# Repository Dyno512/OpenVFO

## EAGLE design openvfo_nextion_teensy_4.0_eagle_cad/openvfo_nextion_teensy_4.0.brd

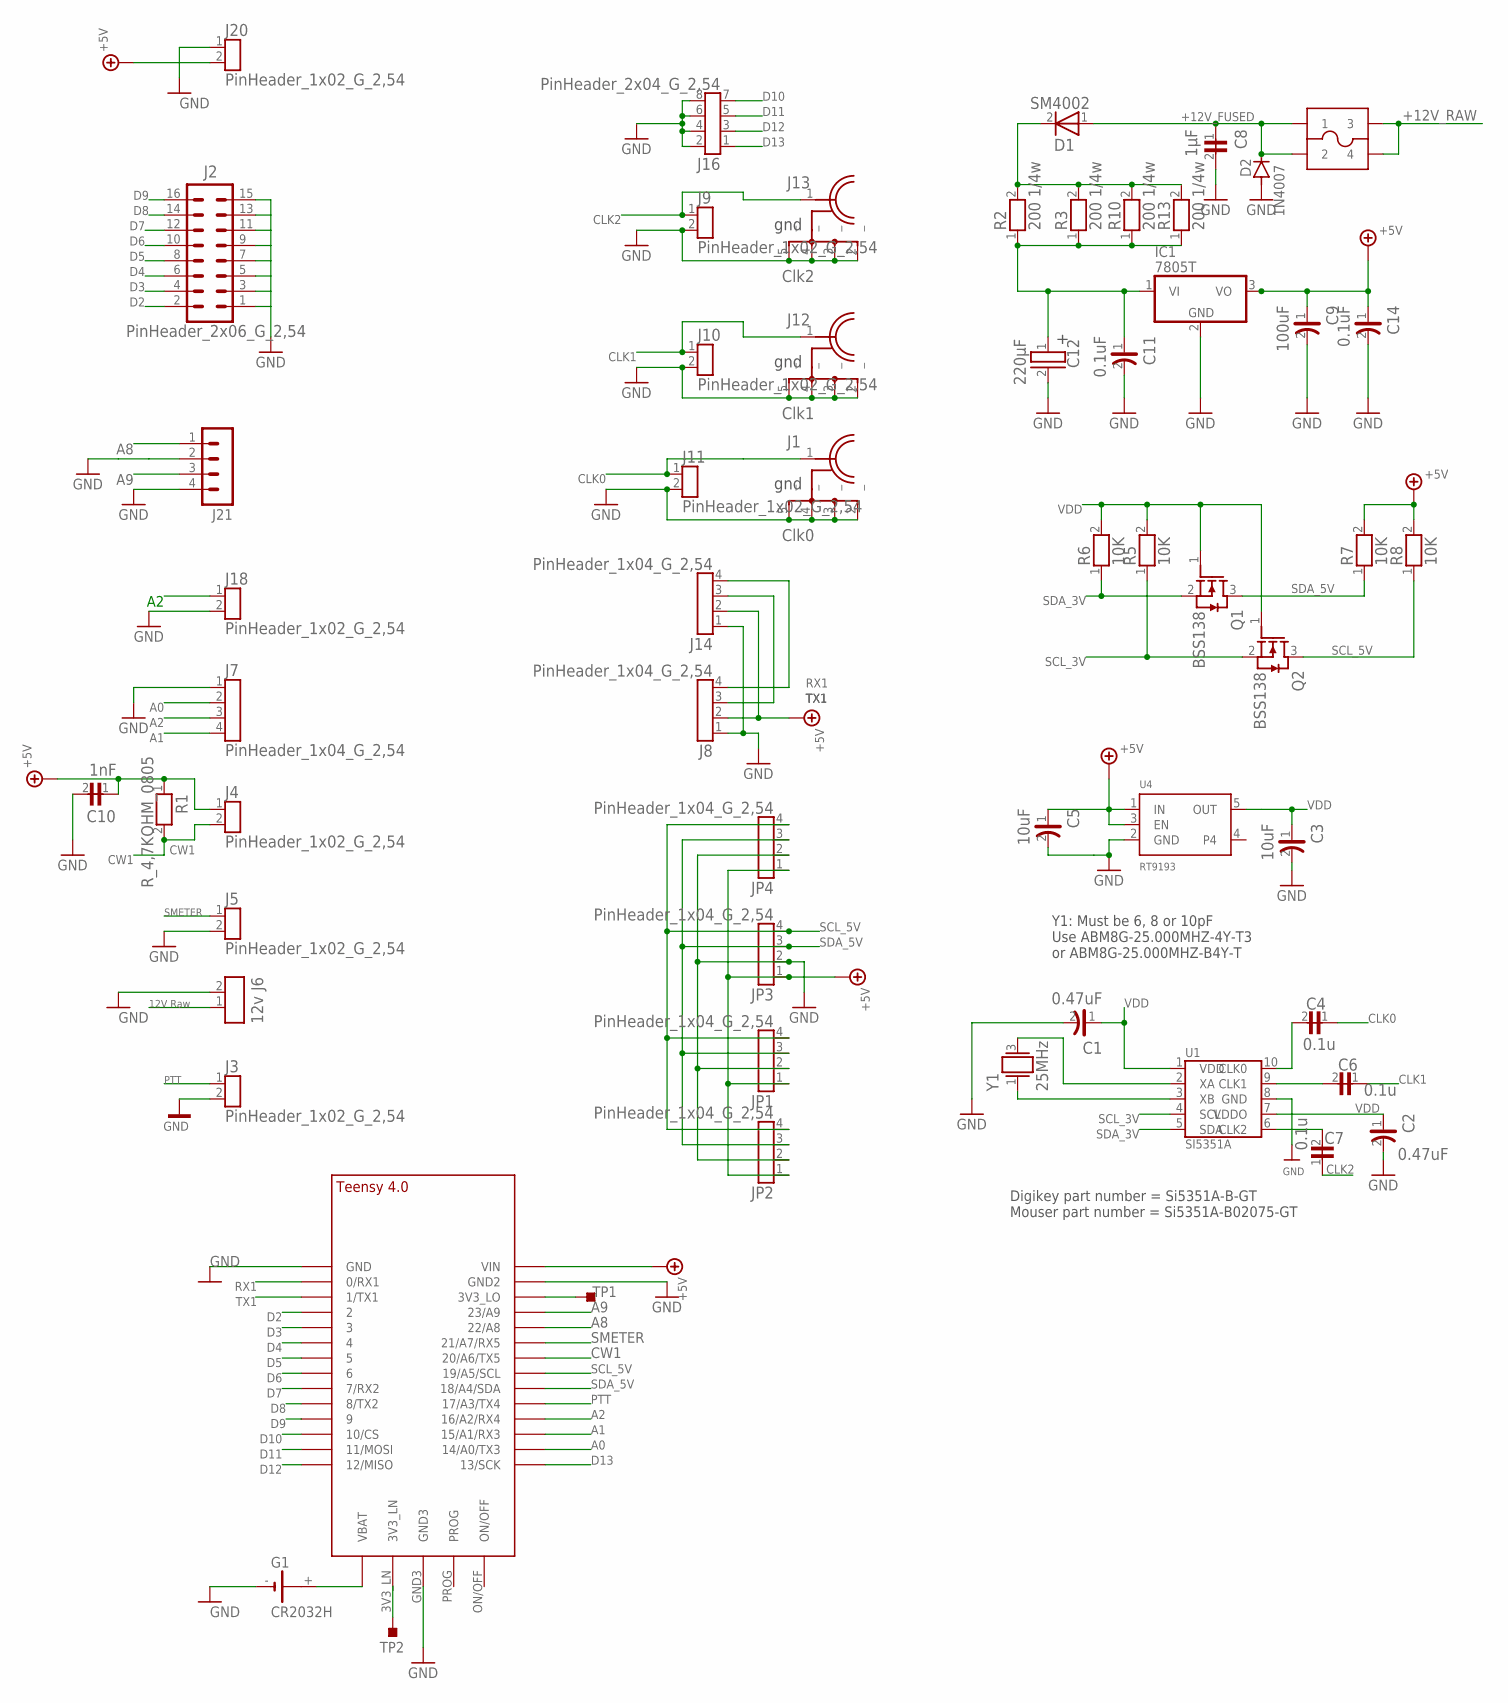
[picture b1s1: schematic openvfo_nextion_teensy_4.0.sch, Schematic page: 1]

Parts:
C1: 0.47uF; 0805_3
C2: 0.47uF; 0805_4
C3: 10uF; 0805_13
C4: 0.1u; 0805_81
C5: 10uF; 0805_12
C6: 0.1u; 0805_82
C7: 0.1u; 0805_83
C8: 1µF; 1206_84
C9: 100uF; 0805_95
C10: 1nF; 0805_23
C11: 0.1uF; 0805_89
C12: 220µF; D8R3,81_ELKO_104
C14: 0.1uF; 0805_96
D1: SM4002; MELF_85
D2: 1N4007; DO41-10
F1: SMALLFUSE
G1: CR2032H
IC1: 7805T; TO220H
J1: Clk0; SMA-EINBAUBUCHSE_67
J2: PinHeader_2x06_G_2,54; MA08-2
J3: PinHeader_1x02_G_2,54; STIFTLEISTE_1X02_G_2,54_17
J4: PinHeader_1x02_G_2,54; STIFTLEISTE_1X02_G_2,54_18
J5: PinHeader_1x02_G_2,54; STIFTLEISTE_1X02_G_2,54_19
J6: 12v; SL-MTA/2.54/2POL_20
J7: PinHeader_1x04_G_2,54; STIFTLEISTE_1X04_G_2,54_15
J8: PinHeader_1x04_G_2,54; STIFTLEISTE_1X04_G_2,54_22
J9: PinHeader_1x02_G_2,54; STIFTLEISTE_1X02_G_2,54_49
J10: PinHeader_1x02_G_2,54; STIFTLEISTE_1X02_G_2,54_50
J11: PinHeader_1x02_G_2,54; STIFTLEISTE_1X02_G_2,54_51
J12: Clk1; SMA-EINBAUBUCHSE_68
J13: Clk2; SMA-EINBAUBUCHSE_69
J14: PinHeader_1x04_G_2,54; STIFTLEISTE_1X04_G_2,54_70
J16: PinHeader_2x04_G_2,54; STIFTLEISTE_2X04_G_2,54_71
J18: PinHeader_1x02_G_2,54; STIFTLEISTE_1X02_G_2,54_97
J20: PinHeader_1x02_G_2,54; STIFTLEISTE_1X02_G_2,54_137
J21: MA04-1
JP1, JP2, JP3, JP4: PinHeader_1x04_G_2,54; STIFTLEISTE_1X04_G_2,54_14
Q1: BSS138; SOT23/3_7
Q2: BSS138; SOT23/3_8
R1: R_4,7KOHM_0805; 0805_21
R2: 200 1/4w; 0805_142
R3: 200 1/4w; 0805_145
R5: 10K; 0805_5
R6: 10K; 0805_6
R7: 10K; 0805_9
R8: 10K; 0805_10
R10: 200 1/4w; 0805_146
R13: 200 1/4w; 0805_147
TP1, TP2: TESTPOINT_TPS-PAD-036; TESTPOINT_PAD-036
U1: SI5351A; MSOP10/WB3X3/P0,5_0
U4: RT9193; SOT23-5_11
U$1: TEENSY_4.0
Y1: 25MHz; CFPX-104_1

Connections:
+5V: C5.1, C9.1, C10.1, C14.1, IC1.3 (VO), J4.1, J8.2, J14.2, J20.2, JP1.1, JP2.1, JP3.1, JP4.1, R1.1, R7.2, R8.2, U4.1 (IN), U4.3 (EN), U$1.VIN
+12V_FUSED: C8.1, D1.1, D2.C, F1.P$1 (1), F1.P$2 (2)
+12V_RAW: F1.P$3 (3), F1.P$4 (4), J6.1
A0: J7.2, U$1.14/A0 (14/A0/TX3)
A1: J7.4, U$1.15/A1 (15/A1/RX3)
A2: J7.3, J18.1, U$1.16/A2 (16/A2/RX4)
A8: J21.1, U$1.22/A8
A9: J21.3, U$1.23/A9
CLK0: C4.1, J1.1, J11.1
CLK1: C6.1, J10.1, J12.1
CLK2: C7.1, J9.1, J13.1
CW1: J4.2, R1.2, U$1.20/A6 (20/A6/TX5)
D2: J2.2, U$1.2
D3: J2.4, U$1.3/CANTX (3)
D4: J2.6, U$1.4/CANRX (4)
D5: J2.8, U$1.5
D6: J2.10, U$1.6
D7: J2.12, U$1.7 (7/RX2)
D8: J2.14, U$1.8 (8/TX2)
D9: J2.16, U$1.9/CS (9)
D10: J16.7, U$1.10/CS
D11: J16.5, U$1.11/MOSI
D12: J16.3, U$1.12/MISO
D13: J16.1, U$1.13/SCK
GND: C1.2, C2.2, C3.2, C5.2, C8.2, C9.2, C10.2, C11.2, C12.2, C14.2, D2.A, G1.-, IC1.2 (GND), J1.2 (_), J1.3 (_), J1.4 (_), J1.5 (_), J2.1, J2.3, J2.5, J2.7, J2.9, J2.11, J2.13, J2.15, J3.2, J5.2, J6.2, J7.1, J8.1, J9.2, J10.2, J11.2, J12.2 (_), J12.3 (_), J12.4 (_), J12.5 (_), J13.2 (_), J13.3 (_), J13.4 (_), J13.5 (_), J14.1, J16.2, J16.4, J16.6, J16.8, J18.2, J20.1, J21.2, J21.4, JP1.2, JP2.2, JP3.2, JP4.2, U1.8 (GND), U4.2 (GND), U$1.GND, U$1.GND2, U$1.GND3
unnamed: TP2.1, U$1.3V3_LN
unnamed: TP1.1, U$1.3V3_LO
unnamed: G1.+, U$1.VBAT\ (VBAT)
PTT: J3.1, U$1.17/A3 (17/A3/TX4)
RX1: J8.4, J14.4, U$1.0/RX (0/RX1)
SCL_3V: Q2.2, R5.1, U1.4 (SCL)
SCL_5V: JP1.4, JP2.4, JP3.4, JP4.4, Q2.3, R8.1, U$1.19/A5/SCL
SDA_3V: Q1.2, R6.1, U1.5 (SDA)
SDA_5V: JP1.3, JP2.3, JP3.3, JP4.3, Q1.3, R7.1, U$1.18/A4/SDA
SIG$152: C4.2, U1.10 (CLK0)
SIG$153: C6.2, U1.9 (CLK1)
SIG$154: C7.2, U1.6 (CLK2)
SIG$156: U1.2 (XA), Y1.3
SIG$165: U1.3 (XB), Y1.1
SIG$193: C11.1, C12.1, IC1.1 (VI), R2.1, R3.1, R10.1, R13.1
SIG$264: D1.2, R2.2, R3.2, R10.2, R13.2
SMETER: J5.1, U$1.21/A7 (21/A7/RX5)
TX1: J8.3, J14.3, U$1.1/TX (1/TX1)
VDD: C1.1, C2.1, C3.1, Q1.1, Q2.1, R5.2, R6.2, U1.1 (VDD), U1.7 (VDDO), U4.5 (OUT)

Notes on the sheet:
Digikey part number = Si5351A-B-GT
Mouser part number = Si5351A-B02075-GT
Y1: Must be 6, 8 or 10pF
Use ABM8G-25.000MHZ-4Y-T3
or ABM8G-25.000MHZ-B4Y-T
PTT
12V Raw
SMETER

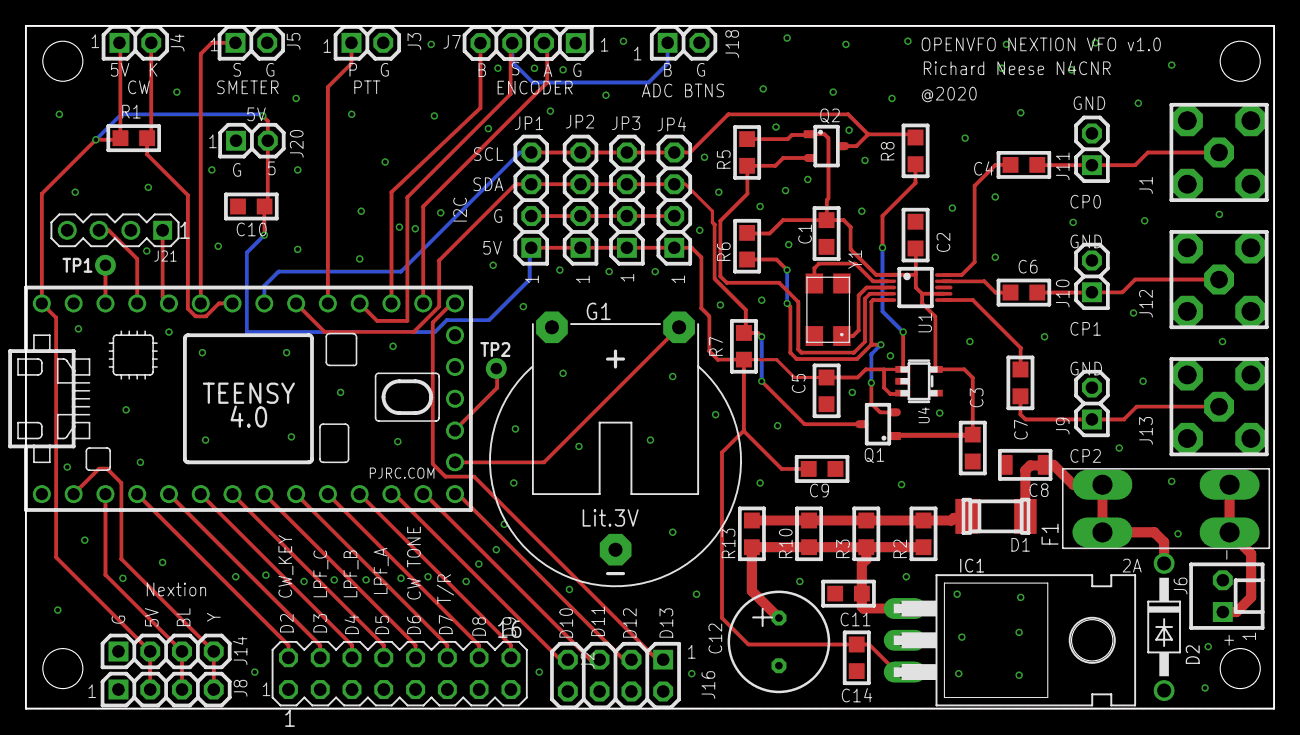
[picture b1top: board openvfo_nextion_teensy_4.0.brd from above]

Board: 2 copper layers, 99.7 x 54.6 mm, 57 parts (0 on the bottom side), 44 nets.

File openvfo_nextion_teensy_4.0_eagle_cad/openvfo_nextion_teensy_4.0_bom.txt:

Partlist

Exported from openvfo_nextion_teensy_4.0.brd at 2/11/2020 10:59 AM

EAGLE Version 9.5.2 Copyright (c) 1988-2019 Autodesk, Inc.

Assembly variant: 

Part     Value                 Package                     Library                Position (mm)         Orientation

C1       0.47uF                0805_3                      TARGET3001!_V20.6.0.4  (64.239 37.973)       R270
C2       0.47uF                0805_4                      TARGET3001!_V20.6.0.4  (71.351 37.846)       R90
C3       10uF                  0805_13                     TARGET3001!_V20.6.0.4  (75.923 20.828)       R270
C4       0.1u                  0805_81                     TARGET3001!_V20.6.0.4  (80.01 43.457)        R180
C5       10uF                  0805_12                     TARGET3001!_V20.6.0.4  (64.239 25.4)         R270
C6       0.1u                  0805_82                     TARGET3001!_V20.6.0.4  (80.01 33.251)        R180
C7       0.1u                  0805_83                     TARGET3001!_V20.6.0.4  (79.733 26.035)       R90
C8       1µF                   1206_84                     TARGET3001!_V20.6.0.4  (80.114 19.483)       R180
C9       100uF                 0805_95                     TARGET3001!_V20.6.0.4  (63.881 19.154)       R0
C10      1nF                   0805_23                     TARGET3001!_V20.6.0.4  (18.265 40.132)       R180
C11      0.1uF                 0805_89                     TARGET3001!_V20.6.0.4  (65.993 9.188)        R180
C12      220µF                 D8R3,81_ELKO_104            TARGET3001!_V20.6.0.4  (60.429 5.334)        R270
C14      0.1uF                 0805_96                     TARGET3001!_V20.6.0.4  (66.652 4.064)        R270
D1       SM4002                MELF_85                     TARGET3001!_V20.6.0.4  (77.781 15.366)       R180
D2       1N4007                DO41-10                     diode                  (91.217 6.525)        R270
F1       SMALLFUSE             SMALLFUSE                   000_ICS                (91.37 15.99)         R0
G1       CR2032H               CR2032H                     battery                (47.371 19.685)       R0
IC1      7805T                 TO220H                      linear                 (80.645 5.461)        R270
J1       Clk0                  SMA-EINBAUBUCHSE_67         TARGET3001!_V20.6.0.4  (95.608 44.45)        R270
J6       12v                   SL-MTA/2.54/2POL_20         TARGET3001!_V20.6.0.4  (95.913 8.99)         R270
J12      Clk1                  SMA-EINBAUBUCHSE_68         TARGET3001!_V20.6.0.4  (95.608 34.29)        R270
J13      Clk2                  SMA-EINBAUBUCHSE_69         TARGET3001!_V20.6.0.4  (95.608 24.13)        R270
J21                            MA04-1                      con-lstb               (7.366 38.227)        R180
Q1       BSS138                SOT23/3_7                   TARGET3001!_V20.6.0.4  (68.349 22.733)       R90
Q2       BSS138                SOT23/3_8                   TARGET3001!_V20.6.0.4  (64.239 44.958)       R270
R1       R_4,7KOHM_0805        0805_21                     TARGET3001!_V20.6.0.4  (8.867 45.593)        R0
R2       200 1/4w              0805_142                    TARGET3001!_V20.6.0.4  (71.986 13.97)        R90
R3       200 1/4w              0805_145                    TARGET3001!_V20.6.0.4  (67.414 13.97)        R90
R5       10K                   0805_5                      TARGET3001!_V20.6.0.4  (57.889 44.45)        R90
R6       10K                   0805_6                      TARGET3001!_V20.6.0.4  (57.889 36.957)       R90
R7       10K                   0805_9                      TARGET3001!_V20.6.0.4  (57.635 28.956)       R270
R8       10K                   0805_10                     TARGET3001!_V20.6.0.4  (71.351 44.577)       R270
R10      200 1/4w              0805_146                    TARGET3001!_V20.6.0.4  (62.842 13.97)        R90
R13      200 1/4w              0805_147                    TARGET3001!_V20.6.0.4  (58.27 13.97)         R90
U1       SI5351A               MSOP10/WB3X3/P0,5_0         TARGET3001!_V20.6.0.4  (71.351 33.655)       R270
U4       RT9193                SOT23-5_11                  TARGET3001!_V20.5.0.73 (71.628 26.162)       R270
Y1       25MHz                 CFPX-104_1                  TARGET3001!_V20.6.0.4  (64.366 31.877)       R90

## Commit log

2020-04-06 Added new files
2020-04-07 Update openvfo.h
    Updated the pinout for use with the teensy 4.0 and OpenVFO
2020-04-07 Adding todo and pinouttxt files
    added todo file and pinout file for referance
2020-04-17 working on openvfo
    working on serial driver
2020-04-20 cleanup
2020-04-25 fixed spelling error
2020-04-25 working on serial driver
2020-04-30 updated hwserial file
2020-04-30 working on serial display driver
    working to replace softserial with hardware serial
2020-04-30 workign on serial port
2020-04-30 new changes
